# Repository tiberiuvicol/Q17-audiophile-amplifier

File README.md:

# Q17-an audiophile approach to perfect sound

<a href="https://github.com/tiberiuvicol/Q17.3">Q17.3 is the latest implementation</a>

Q17 is a class B amplifier based on current dumping principle.<br>
Please refer to <a href="https://github.com/tiberiuvicol/Q17-audiophile-amplifier/blob/main/Project%20description.pdf">Project description.pdf</a> for project description.<br>
Use KiCad 6, or later, to open and edit source files.  KiCad 6 can be downloaded from CERN, https://www.kicad.org<br>
<b>LTSpice</b> - contain simulation asc file<br>
<b>Q17.7z</b> - <a href="https://forum.kicad.info/t/simulation-examples-for-kicad-eeschema-ngspice/34443">ngspice simulation</a> files for Q17. This will run directly in KiCad. Thank you, Holger Vogt !<br>
<b>KiCad source PS</b> - active rectification power supply KiCad source files<br>
<b>KiCad source</b> - Q17 amplifier KiCad source files<br>
<b>Q17_2final</b> - Q17 amplifier KiCad source files for dual output stage<br>
<b>Q17.pdf</b> - detailed presentation - bill of materials included<br>
<b>gerber-ps.zip</b> - production gerber for PCB active rectification power supply<br>
<b>Q17-Gerber.zip</b> - production gerber for Q17 amplifier with single output pair<br>
<a href="https://github.com/tiberiuvicol/Q17-audiophile-amplifier/blob/main/Q17-gerber-2pair.zip"><b>Q17-gerber-2pair.zip</b></a> - production gerber files for Q17 with dual output pair stage<br>
<b>Q17_dimensions.pdf</b> - PDf file with most important PCB dimensions<br>
Important ! - Amplifier is more stable with R32=0ohm

<br>
Click & Order your Q17 with dual output pair PCB @ <br>
Purchase parts (for one channel) with one click from mouser ->> https://www.mouser.com/ProjectManager/ProjectDetail.aspx?AccessID=1f37a45393 <br>
For STEREO or MULTICHANNEL multiply the order with the same parts. <br>
<br>
<br>
<b>Q&A collected from mail</b><br>
<br>
Q: Why no dc blocking input capacitor?<br>
A: <i>Please consider that Q17 first stage make use of an operational that have a C7=1uF capacitor in negative loop. <br>
This already make a dc block and we have a non polar capacitor C2&C22 in dc servo as well.<br>
On other hand, if there is any dc at amplifier input, you should look on your audio source and eliminate it. Do not try to “solve” previous stage problems by "playing safe" at the amplifier input.</i><br>
<br>
<br>
Q: Why no voltage/ESD input protection ?<br>
A: <i>A voltage/ESD can be made by using zener or reverse polarised diodes. The issue with this approach is that any reverse polarised p/n junction (diode etc) will have high parasitic capacitance modulated by voltage and this highly degrade amplifier performance. How to work around this ? Use a good R-2R Volume Controller with constant output impedance.</i><br>
<br>
<br>
Q: Any amplifier need input LPF, otherwise EMI will affect SNR.  Q17 do not have one, therefore it is poorly designed. Why Q17 do not have input LPF?<br>
A: <i>Please do not generalise. The world is not black and white.The role of LPF is to block any unwanted frequencies to enter in amplifier. <br>
A LPF must be designed such way that will not be affected by input impedance. This is not the case with a potentiometer. Does not matter how good this potentiometer is, his attenuation will affect LPF and therefore amplifier bandwidth. This is very audible at low level volume.<br>
The classic way on how a potentiometer is implemented, is that he offer constant input impedance and variable output impedance toward amplifier input. The down side is that, even you go for a high input impedance, at low audio levels input LPF will reach audio band affecting amplifier bandwidth. This is translated in poor audio performance at low audio levels.<br>
This issue was addressed in Maya volume controller that make use of an R-2R resistive network allowing constant output impedance with high input variable impedance.<br>
Beside this, input cable parasitic capacitance together with high amplifier impedance is enough to form a HF-LPF. Output operational LPF at ~125KHz will clean any noise further.</i><br>
<br>
<br>
Q: Could you please recommend me a potentiometer ?<br>
A: <i>Best attenuator will be a R-2R one with constant output impedance. If you want to go cheap please use a 50K log ALPS.</i>
<br>
<br>
Q: Why there is no super diode ?<br>
A: <i>A super diode is usually made with a BJT, where his Vbe variation with temperatures is used to adjust output stage bias. Unfortunately this is highly nonlinear and will modulate, with Vcb voltage (again reverse polarised p/n junction), output stage bias. While this is very efficient, will highly degrade audio performance. My preference is to have plain and simple resistors, with no capacitor decoupling between output mosfet gates.</i><br>
<br>
<br>
Q: What about transitory power ON/OFF ? <br>
A: <i>For this there are Q13&Q14. These have double role.<br>
One is to ensure soft start and soft power off using RC made with R29C13 and R30C14. <br>
This can be seen at amplifier turn on, D1 & D4 will light after ~1s.<br>
Second role for Q13&Q14 is to act as super-capacitors, ensuring smooth power supply for class A and input stage.</i><br>
<br>
<br>
Q: Why no protection zeners on all mosfets ?<br>
A: <i>Some mosfets need Vgs protection while other do not need.<br>
Let’s start with ones that do not need and later the ones that may need.<br>
Q1 and Q4 are part of regulators and Vgs is already limited by 18V zeners.<br>
Q8 is part of cascode and his Vgs is already limited by positive zener regulator to 18V. You may say it is high, but Q8 source is already lifted above ground by Q7.<br>
Q9 and Q11 are part of current mirror. Q9’s Vgs is limited by Q10 + Vbe and Q10 by Q9 Vgs + VR3. This will not exceed 4V.<br>
Q5 Vgs is also limited by Q9 Vds + VR3. Where Q9 Vds = Q10 Vgs. Therefore, mirror with Q9&Q10 act as Vgs limiter for Q5.<br>
Q6 may need a zener to limit his Vgs due during a transitory turn on his Vgs may be higher, but for a soft turn on there are Q13&Q14.<br>
Q13&Q14 obviously need Vgs limiters because at power on, while C13&C14 are charging, Vgs will be above 45V. For such reason there are zener D4&D5, limiting Vgs to a value that keep Q13&Q14 on safe side.<br>
Q15&Q16&Q17&Q18 are output transistors that may need protection zener. These are high transconductance mosfets that indeed will deliver very high transitory currents. Here the man advantage is that we are running these in class B with very low bias current. Turn on/off transitory is also softened by Q13&Q14 trough class A stage made with Q5&Q6.<br>
On other hand, I prefer to run output stage without protection zener, due any zener internal parasitic capacitance is modulated with voltage. Any reverse biased diode act like a varicap. This is translated in muddy highs.</i><br>
<br>
<br>
Q: Why no output inductor ?<br>
A: <i>This is a highly debatable question.<br>
I’m a nerd audiophile. I like good sound more than “playing safe”.<br>
However, your speaker cables have already an important inductance and parasitic capacitance that must considered. <br>
In some particular cases adding an output inductor may be needed, but these are very … few particular ones.<br>
To be short, Q17 with no coil sound better.</i><br>
<br>
<br>
Q: May I use Lateral MOSFET's in ouput stage ?<br>
A: <i>No, you do not, the PCB was designed for Vertical MOSFET. Lateral mosfet transistor's have different piout than Vertical MOSFET.<br>
  PCB need to be redesigned to accomodate Lateral's, for both Class A and output Class B stage.
  Laterals have lower Vgsth than Verticals, hence for laterals, R11 and R12 must be between 9.1 and 10 ohm.</i><br>
<br>
<br>
Q: Why no embedded protection in your schematic ?<br>
A: <i>This again due sound quality. There is always a trade between playing safe and having best sound.<br>
I like to have best sound even I do not play safe and currently market offer a wide range of speaker protection modules.<br>
Simplest protection would be to use a fast fuse (3A-5A) at amplifier output.</i><br>
<br>
<br>
Q: How much capacitance I may put in power supply ?<br>
A: <i>This is related to your power transformer. A huge capacitance must be charged to be efficient.  For a transformer with 3A in secondary, I would say 20mF per rail is enough.</i><br>
<br>
<br>
Q: Is there any sound difference between a normal bridge and Saligny synchronous rectifiers ?<br>
A: <i>Yes, Saligny rectifiers are far superior and bring important sonic improvement.</i>
<br>
<br>
Q: It is Q17 quiet ?<br>
A: <i>Yes it is. No fass no buzz, even with high SPL speakers >95dBm.</i><br>
<br>
<br>
Q: May you recommend a transformer ?<br>
A: <i>Any well made 300VA transformer, with 2 separate secondaries at min.36Vac - max.42Vac.</i><br>
<i>For my projects I order at https://petra-toroid.ro/?lang=en they ship worldwide.</i><br>
<i>How to order:</i><br>
<i>- go to https://petra-toroid.ro/contact/?lang=en use form or email</i><br>
<i>- mention that you want to order one or two 300VA trafo</i><br>
<i>- primary 115Vac or 230Vac, depending on the mains voltage in your region</i><br>
<i>- 2 separate 36Vac secondaries</i><br>
<i>- optional magnetic shielding</i><br>
<i>- mention that application will be for audio</i><br>
<i>Other sources are: https://www.audiophonics.fr/en/toroidal-transformers/toroidal-transformer-300va-2x38v-p-5548.html</i><br>
<i>Toroidy https://sklep.toroidy.pl/en_US/c/Toroidal-transformers-SUPREME-AUDIO-GRADE-V2/99</i><br>
<i>Trafco http://www.trafco.rs/torusni-en.php</i><br>
<br>
<br>
Q: Can Q17 drive ESL speakers ?<br>
A: <i>Yes, will drive ESL speakers very well. Thanks to high transconductance mosfet’s, Q17 will offer excellent performance on ESl speakers.</i><br>
<br>
<br>
Q: What make Q17 special ?<br>
A: <i>His topology, class B operation, PCB with embedded coil and innovative active power supply. </i><br>
<br>
<br>
Q: Is Q17 power eficient ?<br>
A: <i>Yes, it is. Thanks to class B operation and Saligny synchronous rectification, Q17 is a modern amplifier with low power consumption.</i><br>
<br>
<br>
Q: My left channel is warmer, ~5Celsius, than the right channel. How I can match them ?<br>
A: <i>Is this a really issue ? No.
Left/Right channel temperature difference is mainly due slightly different "bias" in output stage. Even Q17 is running in class B, each mosfet have different Vgs treshold and this is translated in more or less Ids current. You may start by matching Q12 to have very appropiate Vbe's, than make sure R11, R12, R13 are matching R11, R12, R13 from other channel. Finnaly, match output Q15 .. Q18 mosfets between channels.</i><br>
<br>
<br>
Q: Voltage over R3 should be around 0.6Vdc, but mine is way off, how may I adjust this ?<br>
A: <i>In order to have 0.6Vdc over R3, Q9 and Q11 must be matched (same Vgth), only then voltage over R3 is given only by Q10Vbe. Therefore please match Q9 and Q11 to have same Vgsth=Voltage gate to source threshold. </i><br>
<br>
<br>
Q: Where you you place this amplifier in term of value ?<br>
A: <i>A well executed Q17, will be better or at least on pair with some $5 digit amplifiers.</i><br>
<br>
<br>
Thank you for reading ! <br>
If you have built this amplifier I would love to see your Q17 implementation. :-) <br>
<br>
Many thanks to those who built Q17 and shared their experience. Here is the builders feedback:<br>
https://www.diyaudio.com/community/threads/q17-an-audiophile-approach-to-perfect-sound.374507/page-72#post-7179645
<br>
https://www.diyaudio.com/community/threads/q17-an-audiophile-approach-to-perfect-sound.374507/page-114#post-7559688
<br>

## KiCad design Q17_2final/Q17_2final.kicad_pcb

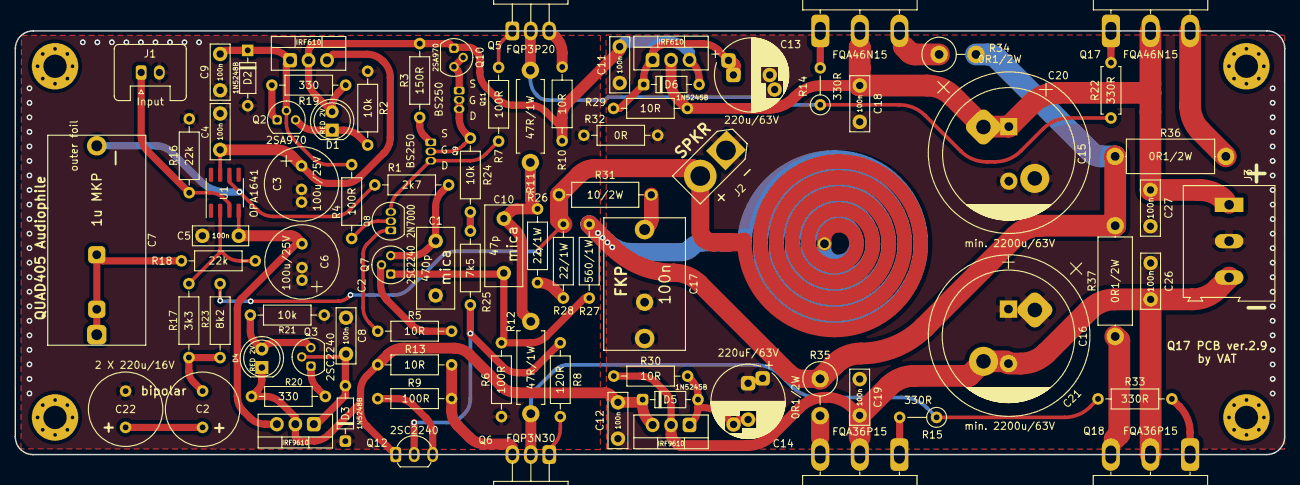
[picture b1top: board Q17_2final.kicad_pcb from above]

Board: 2 copper layers, 174.7 x 58.3 mm, 94 parts (0 on the bottom side), 53 nets.

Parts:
C1: 470p; C_Disc_D11.0mm_W5.0mm_P7.50mm
C2: 220uF/16V; C_Radial_D10.0mm_H12.5mm_P5.00mm
C3, C6: 100u/25V; C_Radial_D10.0mm_H12.5mm_P5.00mm
C4, C5, C8, C9, C11, C12, C18, C19, C26, C27: 100n; C_Disc_D7.5mm_W2.5mm_P5.00mm
C7: 1u MKP; CP_Axial_L20.0mm_D13.0mm_P26.00mm_Horizontal
C10: 47p; C_Disc_D11.0mm_W5.0mm_P7.50mm
C13: 220u/63V; CP_Radial_D10.0mm_P5.00mm_P7.50mm
C14: 220uF/63V; CP_Radial_D10.0mm_P5.00mm_P7.50mm
C15, C16: 2200uF/63V; CP_Radial_D18.0mm_P7.50mm
C17: 100n; C_Rect_L18.0mm_W11.0mm_P15.00mm_FKS3_FKP3
C20, C21: min. 2200u/63V; CP_Radial_D22.0mm_P10.00mm_SnapIn
C22: 2 X 220u/16V; C_Radial_D10.0mm_H12.5mm_P5.00mm
D1, D4: RED 2V; LED_D5.0mm_Clear
D2, D3: 1N5248B; D_DO-35_SOD27_P7.62mm_Horizontal
D5, D6: 1N5245B; D_DO-35_SOD27_P7.62mm_Horizontal
H1, H1#2, H1#3, H1#4: MountingHole; MountingHole_3.2mm_M3_Pad_Via
J1: Input; Stocko_MKS_1651-6-0-202_1x2_P2.50mm_Vertical
J2: Screw_Terminal_01x02; AMASS_XT30U-F_1x02_P5.0mm_Vertical
J3: Screw_Terminal_01x03; TerminalBlock_Altech_AK300-3_P5.00mm
L1: 1u2; L_new
Q1, Q13: IRF610; TO-220-3_Vertical
Q2, Q10: 2SA970; TO-92
Q3, Q7: 2SC2240; TO-92
Q4, Q14: IRF9610; TO-220-3_Vertical
Q5: FQP3P20; TO-220-3_Horizontal_TabDown
Q6: FQP3N30; TO-220-3_Horizontal_TabDown
Q8: 2N7000; TO-92_Inline
Q9, Q11: BS250; TO-92L_Inline
Q12: 2SC2240; TO-92L_Inline_Wide
Q15, Q17: FQA46N15; TO-3P-3_Horizontal_TabDown
Q16, Q18: FQA36P15; TO-3P-3_Horizontal_TabDown
R1: 2k7; R_Axial_DIN0207_L6.3mm_D2.5mm_P10.16mm_Horizontal
R2, R21, R24: 10k; R_Axial_DIN0207_L6.3mm_D2.5mm_P10.16mm_Horizontal
R3: 150R; R_Axial_DIN0207_L6.3mm_D2.5mm_P10.16mm_Horizontal
R4, R6, R7, R9: 100R; R_Axial_DIN0207_L6.3mm_D2.5mm_P10.16mm_Horizontal
R5, R10, R13, R29, R30: 10R; R_Axial_DIN0207_L6.3mm_D2.5mm_P10.16mm_Horizontal
R8: 120R; R_Axial_DIN0207_L6.3mm_D2.5mm_P10.16mm_Horizontal
R11, R12: 47R/1W; R_Axial_DIN0411_L9.9mm_D3.6mm_P12.70mm_Horizontal
R14, R15: 330R; R_Axial_DIN0207_L6.3mm_D2.5mm_P5.08mm_Vertical
R16, R18: 22k; R_Axial_DIN0207_L6.3mm_D2.5mm_P10.16mm_Horizontal
R17: 3k3; R_Axial_DIN0207_L6.3mm_D2.5mm_P10.16mm_Horizontal
R19, R20: 330; R_Axial_DIN0207_L6.3mm_D2.5mm_P10.16mm_Horizontal
R22: 330R; R_Axial_DIN0207_L6.3mm_D2.5mm_P7.62mm_Horizontal
R23: 8k2; R_Axial_DIN0207_L6.3mm_D2.5mm_P10.16mm_Horizontal
R25: 7k5; R_Axial_DIN0207_L6.3mm_D2.5mm_P10.16mm_Horizontal
R26, R28: 22/1W; R_Axial_DIN0207_L6.3mm_D2.5mm_P10.16mm_Horizontal
R27: 560/1W; R_Axial_DIN0207_L6.3mm_D2.5mm_P10.16mm_Horizontal
R31: 10/2W; R_Axial_DIN0309_L9.0mm_D3.2mm_P12.70mm_Horizontal
R32: 0R; R_Axial_DIN0207_L6.3mm_D2.5mm_P10.16mm_Horizontal
R33: 330R; R_Axial_DIN0207_L6.3mm_D2.5mm_P10.16mm_Horizontal
R34, R35: 0R1/2W; R_Axial_DIN0414_L11.9mm_D4.5mm_P5.08mm_Vertical
R36, R37: 0R1/2W; R_Axial_DIN0414_L11.9mm_D4.5mm_P15.24mm_Horizontal
U1: OPA1641; SOIC-8_3.9x4.9mm_P1.27mm

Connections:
GND: C1.2, C3.2, C4.1, C5.1, C6.1, C8.1, C9.1, C22.1, D2.2 (A), D3.1 (K), J1.1, R2.2, R6.2, R16.1, R21.2, R32.1
GNDPWR: C11.1, C12.1, C13.2, C14.1, C15.2, C16.1, C17.2, C18.1, C19.2, C20.2, C21.1, C26.2, C27.1, J2.1, J3.2, R32.2
unnamed: C1.1, Q7.3 (B), R1.2
unnamed: C2.1, R17.1, R23.1
unnamed: C2.2, C22.2
unnamed: C3.1, C4.2, Q1.3 (S), U1.7 (V+)
unnamed: C5.2, C6.2, Q4.3 (S), U1.4 (V-)
unnamed: C7.1, R1.1, U1.6
unnamed: C7.2, R18.2
unnamed: C8.2, D3.2 (A), Q3.2 (C), Q4.1 (G)
unnamed: C9.2, D2.1 (K), Q1.1 (G), Q2.2 (C), R4.1
unnamed: C10.1, R11.2, R12.1, R26.1
unnamed: C10.2, Q7.1 (E), R6.1, R27.1
unnamed: C11.2, D1.2 (A), D6.2 (A), Q1.2 (D), Q10.1 (E), Q13.3 (S), R3.1, R10.1, R19.1
unnamed: C12.2, D4.1 (K), D5.1 (K), Q4.2 (D), Q12.1 (E), Q14.3 (S), R13.2, R20.1
unnamed: C13.1, D6.1 (K), Q13.1 (G), R29.2
unnamed: C14.2, D5.2 (A), Q14.1 (G), R30.1
unnamed: C15.1, C18.2, C20.1, C27.2, J3.1, Q13.2 (D), Q15.2 (D), Q17.2 (D), R29.1
unnamed: C16.2, C19.1, C21.2, C26.1, J3.3, Q14.2 (D), Q16.2 (D), Q18.2 (D), R30.2
unnamed: C17.1, R31.2
unnamed: D1.1 (K), Q2.3 (B), R2.1
unnamed: D4.2 (A), Q3.3 (B), R21.1
unnamed: J1.2, R16.2, U1.3 (+)
unnamed: J2.2, L1.1, R23.2, R28.2, R31.1
unnamed: L1.2, R27.2, R34.2, R35.1, R36.2, R37.1
unnamed: Q2.1 (E), R19.2
unnamed: Q3.1 (E), R20.2
unnamed: Q5.1 (G), R7.2
unnamed: Q5.2 (D), R11.1, R14.1, R22.1
unnamed: Q5.3 (S), R10.2
unnamed: Q6.1 (G), R8.2
unnamed: Q6.2 (D), R12.2, R15.1, R33.1
unnamed: Q6.3 (S), R9.2, R13.1
unnamed: Q7.2 (C), R5.2
unnamed: Q8.1 (S), R5.1
unnamed: Q8.2 (G), R4.2
unnamed: Q8.3 (D), Q9.3 (D), R7.1
unnamed: Q9.1 (S), R3.2
unnamed: Q10.2 (C), Q10.3 (B), Q11.1 (S)
unnamed: Q9.2 (G), Q11.2 (G), Q11.3 (D), R24.1
unnamed: Q12.2 (C), R8.1, R25.2
unnamed: Q12.3 (B), R9.1
unnamed: Q15.1 (G), R14.2
unnamed: Q15.3 (S), R34.1
unnamed: Q16.1 (G), R15.2
unnamed: Q16.3 (S), R35.2
unnamed: Q17.1 (G), R22.2
unnamed: Q17.3 (S), R36.1
unnamed: Q18.1 (G), R33.2
unnamed: Q18.3 (S), R37.2
unnamed: R17.2, R18.1, U1.2 (-)
unnamed: R24.2, R25.1
unnamed: R26.2, R28.1

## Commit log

2022-07-22 latest gerber files for 2 final output stage
2022-12-24 Q17 pcb dimensions
    Q17 pcb dimensions indicate most important parts max. size, distance between holes and placement.
2022-12-28 Update README.md
    Please read before starting this project.
2022-12-29 Added transformer ordering info in Q&A
2022-12-31 Latest Q17 PCB version 2.8
2022-12-31 Latest KiCad files for PCB ver.2.8
2022-12-31 KiCad files for Q17 2 pair pcb ver.2.8
2022-12-31 Production files for Q17 pcb ver.2.8
2023-05-09 updated and corrected with ChatGPT
2023-05-10 Gerber files for Q17 pcb ver.2.9
2023-06-21 Update README.md
    more Q&A have been added.
2023-06-21 Update README.md
    More Q&A added
2023-06-23 Update README.md
    new pic.
